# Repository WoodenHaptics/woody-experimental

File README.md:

# woody-experimental
Experimental code etc under development - do not use

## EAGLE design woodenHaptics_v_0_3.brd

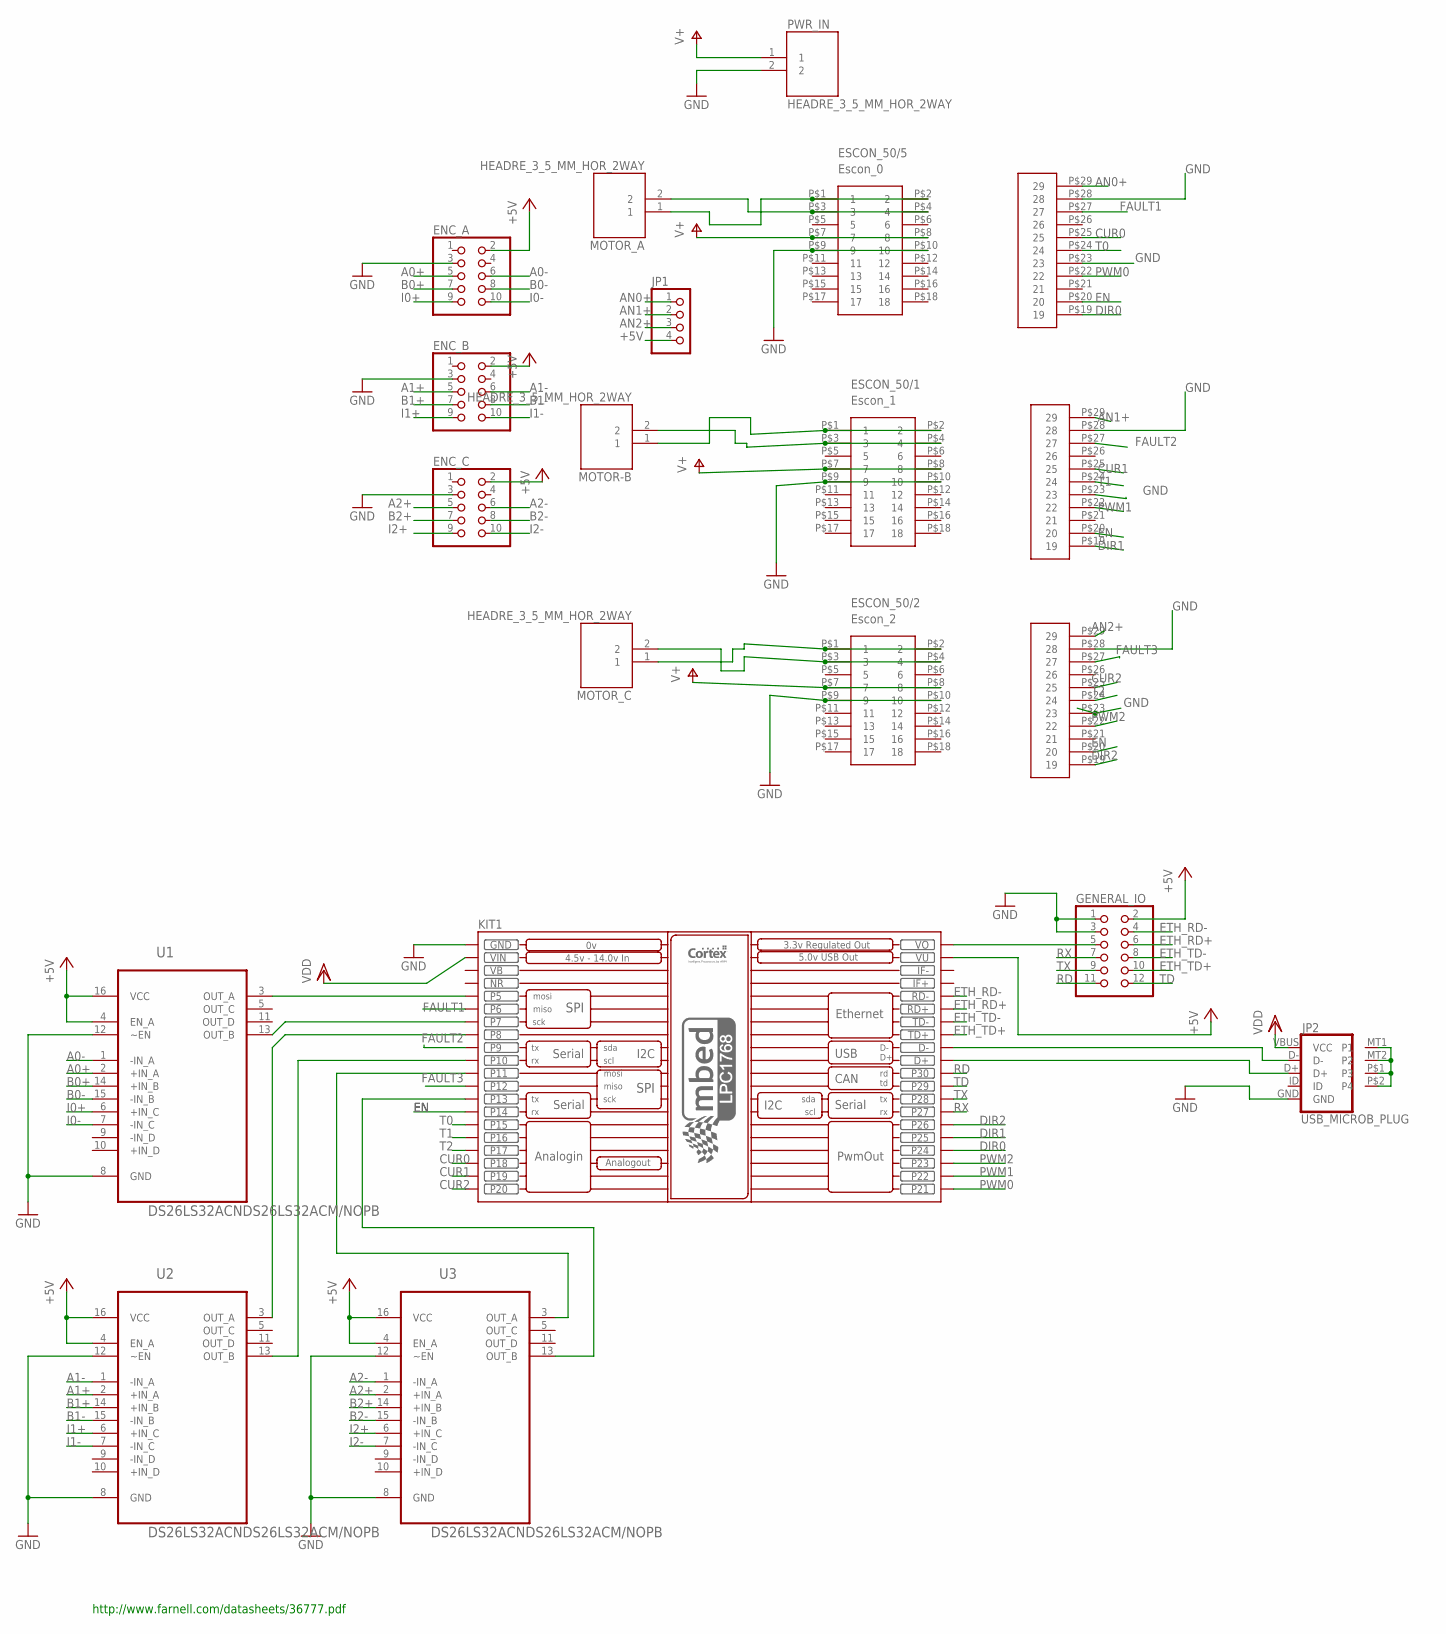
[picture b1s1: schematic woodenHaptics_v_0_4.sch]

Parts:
ENC_A: PINHD-2X5; 2X05
ENC_B: PINHD-2X5; 2X05
ENC_C: PINHD-2X5; 2X05
ESCON_50/1: Escon_1; MODULE
ESCON_50/2: Escon_2; MODULE
ESCON_50/5: Escon_0; MODULE
GENERAL_IO: PINHD-2X6; 2X06
JP1: PINHD-1X4; 1X04
JP2: USB_MICROB_PLUG; USB-MICROB
KIT1: MBED_NXP_LPC1768; MBED-KIT
MOTOR-B: HEADRE_3_5_MM_HOR_2WAY; HEADER_3_5MM_HOR_2WAY
MOTOR_A: HEADRE_3_5_MM_HOR_2WAY; HEADER_3_5MM_HOR_2WAY
MOTOR_C: HEADRE_3_5_MM_HOR_2WAY; HEADER_3_5MM_HOR_2WAY
PWR_IN: HEADRE_3_5_MM_HOR_2WAY; HEADER_3_5MM_HOR_2WAY
U1, U2, U3: DS26LS32ACNDS26LS32ACM/NOPB; M16

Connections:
+5V: ENC_A.2, ENC_B.2, ENC_C.2, GENERAL_IO.2, JP1.4, KIT1.VU, U1.4 (EN_A), U1.16 (VCC), U2.4 (EN_A), U2.16 (VCC), U3.4 (EN_A), U3.16 (VCC)
A0+: ENC_A.5, U1.2 (+IN_A)
A0-: ENC_A.6, U1.1 (-IN_A)
A1+: ENC_B.5, U2.2 (+IN_A)
A1-: ENC_B.6, U2.1 (-IN_A)
A2+: ENC_C.5, U3.2 (+IN_A)
A2-: ENC_C.6, U3.1 (-IN_A)
AN0+: ESCON_50/5.P$29 (29), JP1.1
AN1+: ESCON_50/1.P$29 (29), JP1.2
AN2+: ESCON_50/2.P$29 (29), JP1.3
B0+: ENC_A.7, U1.14 (+IN_B)
B0-: ENC_A.8, U1.15 (-IN_B)
B1+: ENC_B.7, U2.14 (+IN_B)
B1-: ENC_B.8, U2.15 (-IN_B)
B2+: ENC_C.7, U3.14 (+IN_B)
B2-: ENC_C.8, U3.15 (-IN_B)
CUR0: ESCON_50/5.P$25 (25), KIT1.P$18 (P18)
CUR1: ESCON_50/1.P$25 (25), KIT1.P$19 (P19)
CUR2: ESCON_50/2.P$25 (25), KIT1.P$20 (P20)
DIR0: ESCON_50/5.P$19 (19), KIT1.P$24 (P24)
DIR1: ESCON_50/1.P$19 (19), KIT1.P$25 (P25)
DIR2: ESCON_50/2.P$19 (19), KIT1.P$26 (P26)
EN: ESCON_50/1.P$20 (20), ESCON_50/2.P$20 (20), ESCON_50/5.P$20 (20), KIT1.P$14 (P14)
ETH_RD+: GENERAL_IO.6, KIT1.RD+
ETH_RD-: GENERAL_IO.4, KIT1.RD-
ETH_TD+: GENERAL_IO.10, KIT1.TD+
ETH_TD-: GENERAL_IO.8, KIT1.TD-
FAULT1: ESCON_50/5.P$27 (27), KIT1.P$6 (P6)
FAULT2: ESCON_50/1.P$27 (27), KIT1.P$9 (P9)
FAULT3: ESCON_50/2.P$27 (27), KIT1.P$12 (P12)
GND: ENC_A.3, ENC_B.3, ENC_C.3, ESCON_50/1.P$9 (9), ESCON_50/1.P$10 (10), ESCON_50/1.P$23 (23), ESCON_50/1.P$28 (28), ESCON_50/2.P$9 (9), ESCON_50/2.P$10 (10), ESCON_50/2.P$23 (23), ESCON_50/2.P$28 (28), ESCON_50/5.P$9 (9), ESCON_50/5.P$10 (10), ESCON_50/5.P$23 (23), ESCON_50/5.P$28 (28), GENERAL_IO.1, GENERAL_IO.3, JP2.GND, KIT1.GND, PWR_IN.2, U1.8 (GND), U1.12 (~EN), U2.8 (GND), U2.12 (~EN), U3.8 (GND), U3.12 (~EN)
I0+: ENC_A.9, U1.6 (+IN_C)
I0-: ENC_A.10, U1.7 (-IN_C)
I1+: ENC_B.9, U2.6 (+IN_C)
I1-: ENC_B.10, U2.7 (-IN_C)
I2+: ENC_C.9, U3.6 (+IN_C)
I2-: ENC_C.10, U3.7 (-IN_C)
MT: JP2.MT1 (P1), JP2.MT2 (P2), JP2.P$1 (P3), JP2.P$2 (P4)
unnamed: ESCON_50/5.P$3 (3), ESCON_50/5.P$4 (4), MOTOR_A.2
unnamed: ESCON_50/1.P$1 (1), ESCON_50/1.P$2 (2), MOTOR-B.1
unnamed: JP2.D-, KIT1.D-
unnamed: ESCON_50/1.P$3 (3), ESCON_50/1.P$4 (4), MOTOR-B.2
unnamed: ESCON_50/2.P$1 (1), ESCON_50/2.P$2 (2), MOTOR_C.1
unnamed: ESCON_50/2.P$3 (3), ESCON_50/2.P$4 (4), MOTOR_C.2
unnamed: JP2.D+, KIT1.D+
unnamed: KIT1.P$8 (P8), U2.3 (OUT_A)
unnamed: GENERAL_IO.5, KIT1.VOUT (VO)
unnamed: KIT1.P$5 (P5), U1.3 (OUT_A)
unnamed: KIT1.P$7 (P7), U1.13 (OUT_B)
unnamed: KIT1.P$10 (P10), U2.13 (OUT_B)
unnamed: KIT1.P$11 (P11), U3.3 (OUT_A)
unnamed: KIT1.P$13 (P13), U3.13 (OUT_B)
unnamed: ESCON_50/5.P$1 (1), ESCON_50/5.P$2 (2), MOTOR_A.1
NR: KIT1.NR
PWM0: ESCON_50/5.P$22 (22), KIT1.P$21 (P21)
PWM1: ESCON_50/1.P$22 (22), KIT1.P$22 (P22)
PWM2: ESCON_50/2.P$22 (22), KIT1.P$23 (P23)
RD: GENERAL_IO.11, KIT1.P$30 (P30)
RX: GENERAL_IO.7, KIT1.P$27 (P27)
T0: ESCON_50/5.P$24 (24), KIT1.P$15 (P15)
T1: ESCON_50/1.P$24 (24), KIT1.P$16 (P16)
T2: ESCON_50/2.P$24 (24), KIT1.P$17 (P17)
TD: GENERAL_IO.12, KIT1.P$29 (P29)
TX: GENERAL_IO.9, KIT1.P$28 (P28)
V+: ESCON_50/1.P$7 (7), ESCON_50/1.P$8 (8), ESCON_50/2.P$7 (7), ESCON_50/2.P$8 (8), ESCON_50/5.P$7 (7), ESCON_50/5.P$8 (8), PWR_IN.1
VB: KIT1.VB
VDD: JP2.VBUS (VCC), KIT1.VIN

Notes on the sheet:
http://www.farnell.com/datasheets/36777.pdf

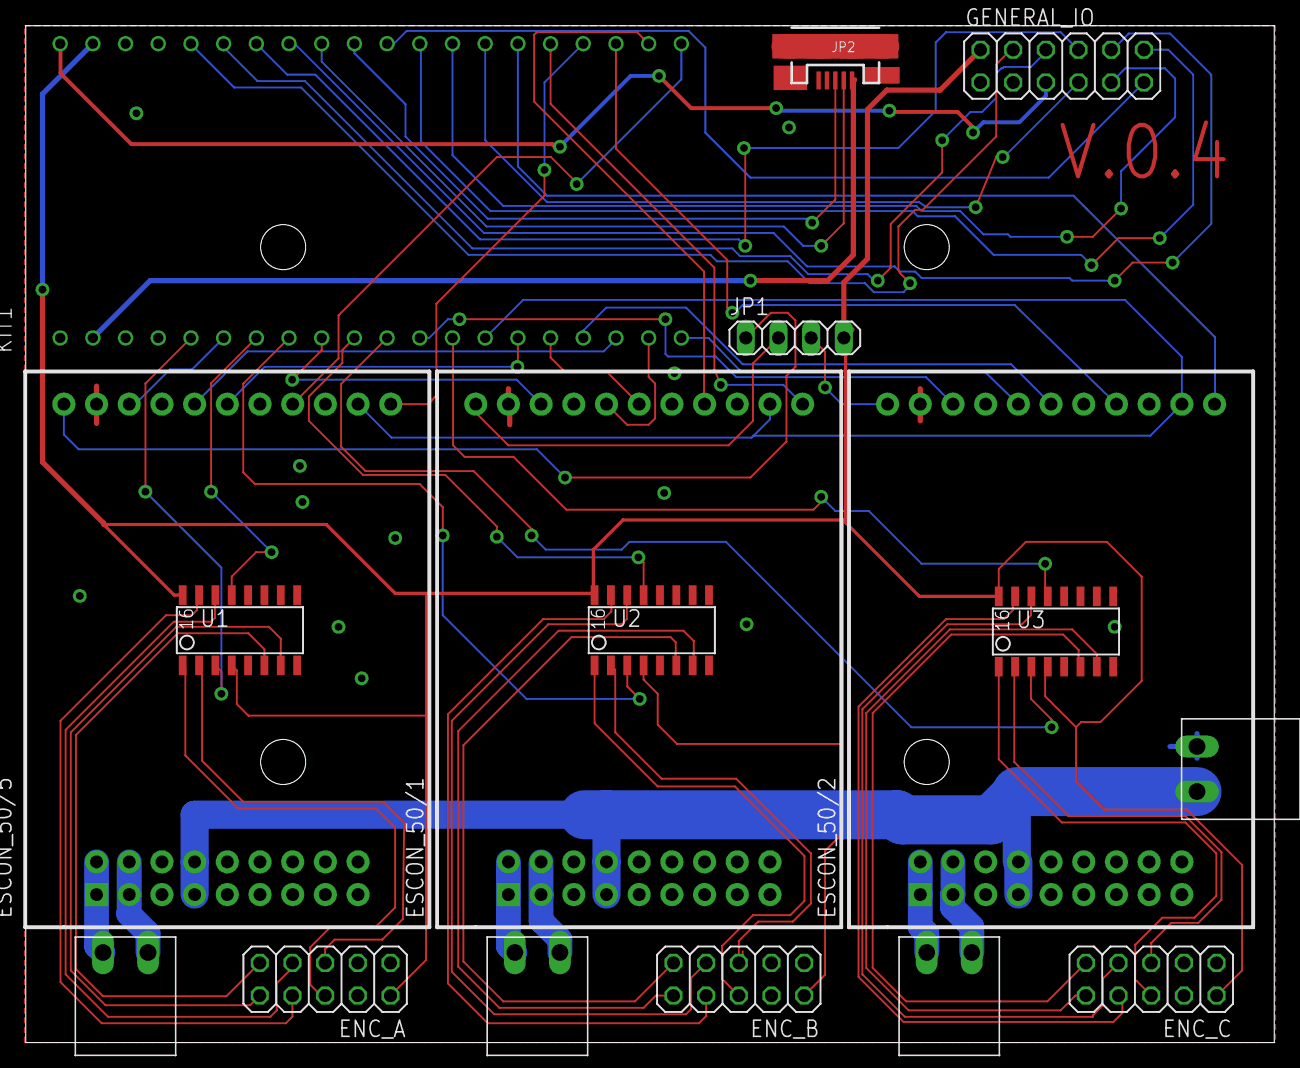
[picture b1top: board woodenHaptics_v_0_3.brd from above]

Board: 2 copper layers, 97.0 x 79.0 mm, 17 parts (0 on the bottom side), 65 nets.

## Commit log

2015-08-12 chai
2015-08-12 current hack from aug 10, 2015
2015-08-12 opens in qtcreator
2016-01-07 works with analoge DAQ extension board 0.3
2016-01-07 with files
2016-01-13 pwm test
2016-01-13 pwm example
2016-01-26 pwm works
2016-09-16 aluhaptics works
2016-09-16 some mods
2016-12-12 works with usb using woodenhaptics 2016 edition on ninja laptop
2016-12-12 x3dom based simulation of woodehaptics motion
2016-12-13 slightly updated
2016-12-13 ok ignore these
2016-12-13 mbed code (archive/reference)
2016-12-15 reading position works with usb and aluhaptics
2016-12-15 amazingly it works
2016-12-15 Rename woodenHaptics_v_0_3.brd to woodenHaptics_v_0_4.brd
2016-12-15 Rename woodenHaptics_v_0_3.sch to woodenHaptics_v_0_4.sch
2017-03-16 some working stuff
2017-03-16 default is woody 2016 including generated json file
2018-11-15 to hack
2018-11-30 pid hack working
2019-01-04 tested ok
2019-01-10 ix as general input
2019-01-29 with filter it works
2019-05-18 usb hid code refreshed
2019-07-09 gimbal ssi test etc

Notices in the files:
parts and their libraries:
SparkFun-Connectors: Licensing: CC v3.0 Share-Alike You are welcome to use this library for commercial purposes.
